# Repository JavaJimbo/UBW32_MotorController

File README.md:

# UBW32_MotorController
Motor control board based on PIC 32MX795 which provides PWM outputs to Cytron MD13s Boards

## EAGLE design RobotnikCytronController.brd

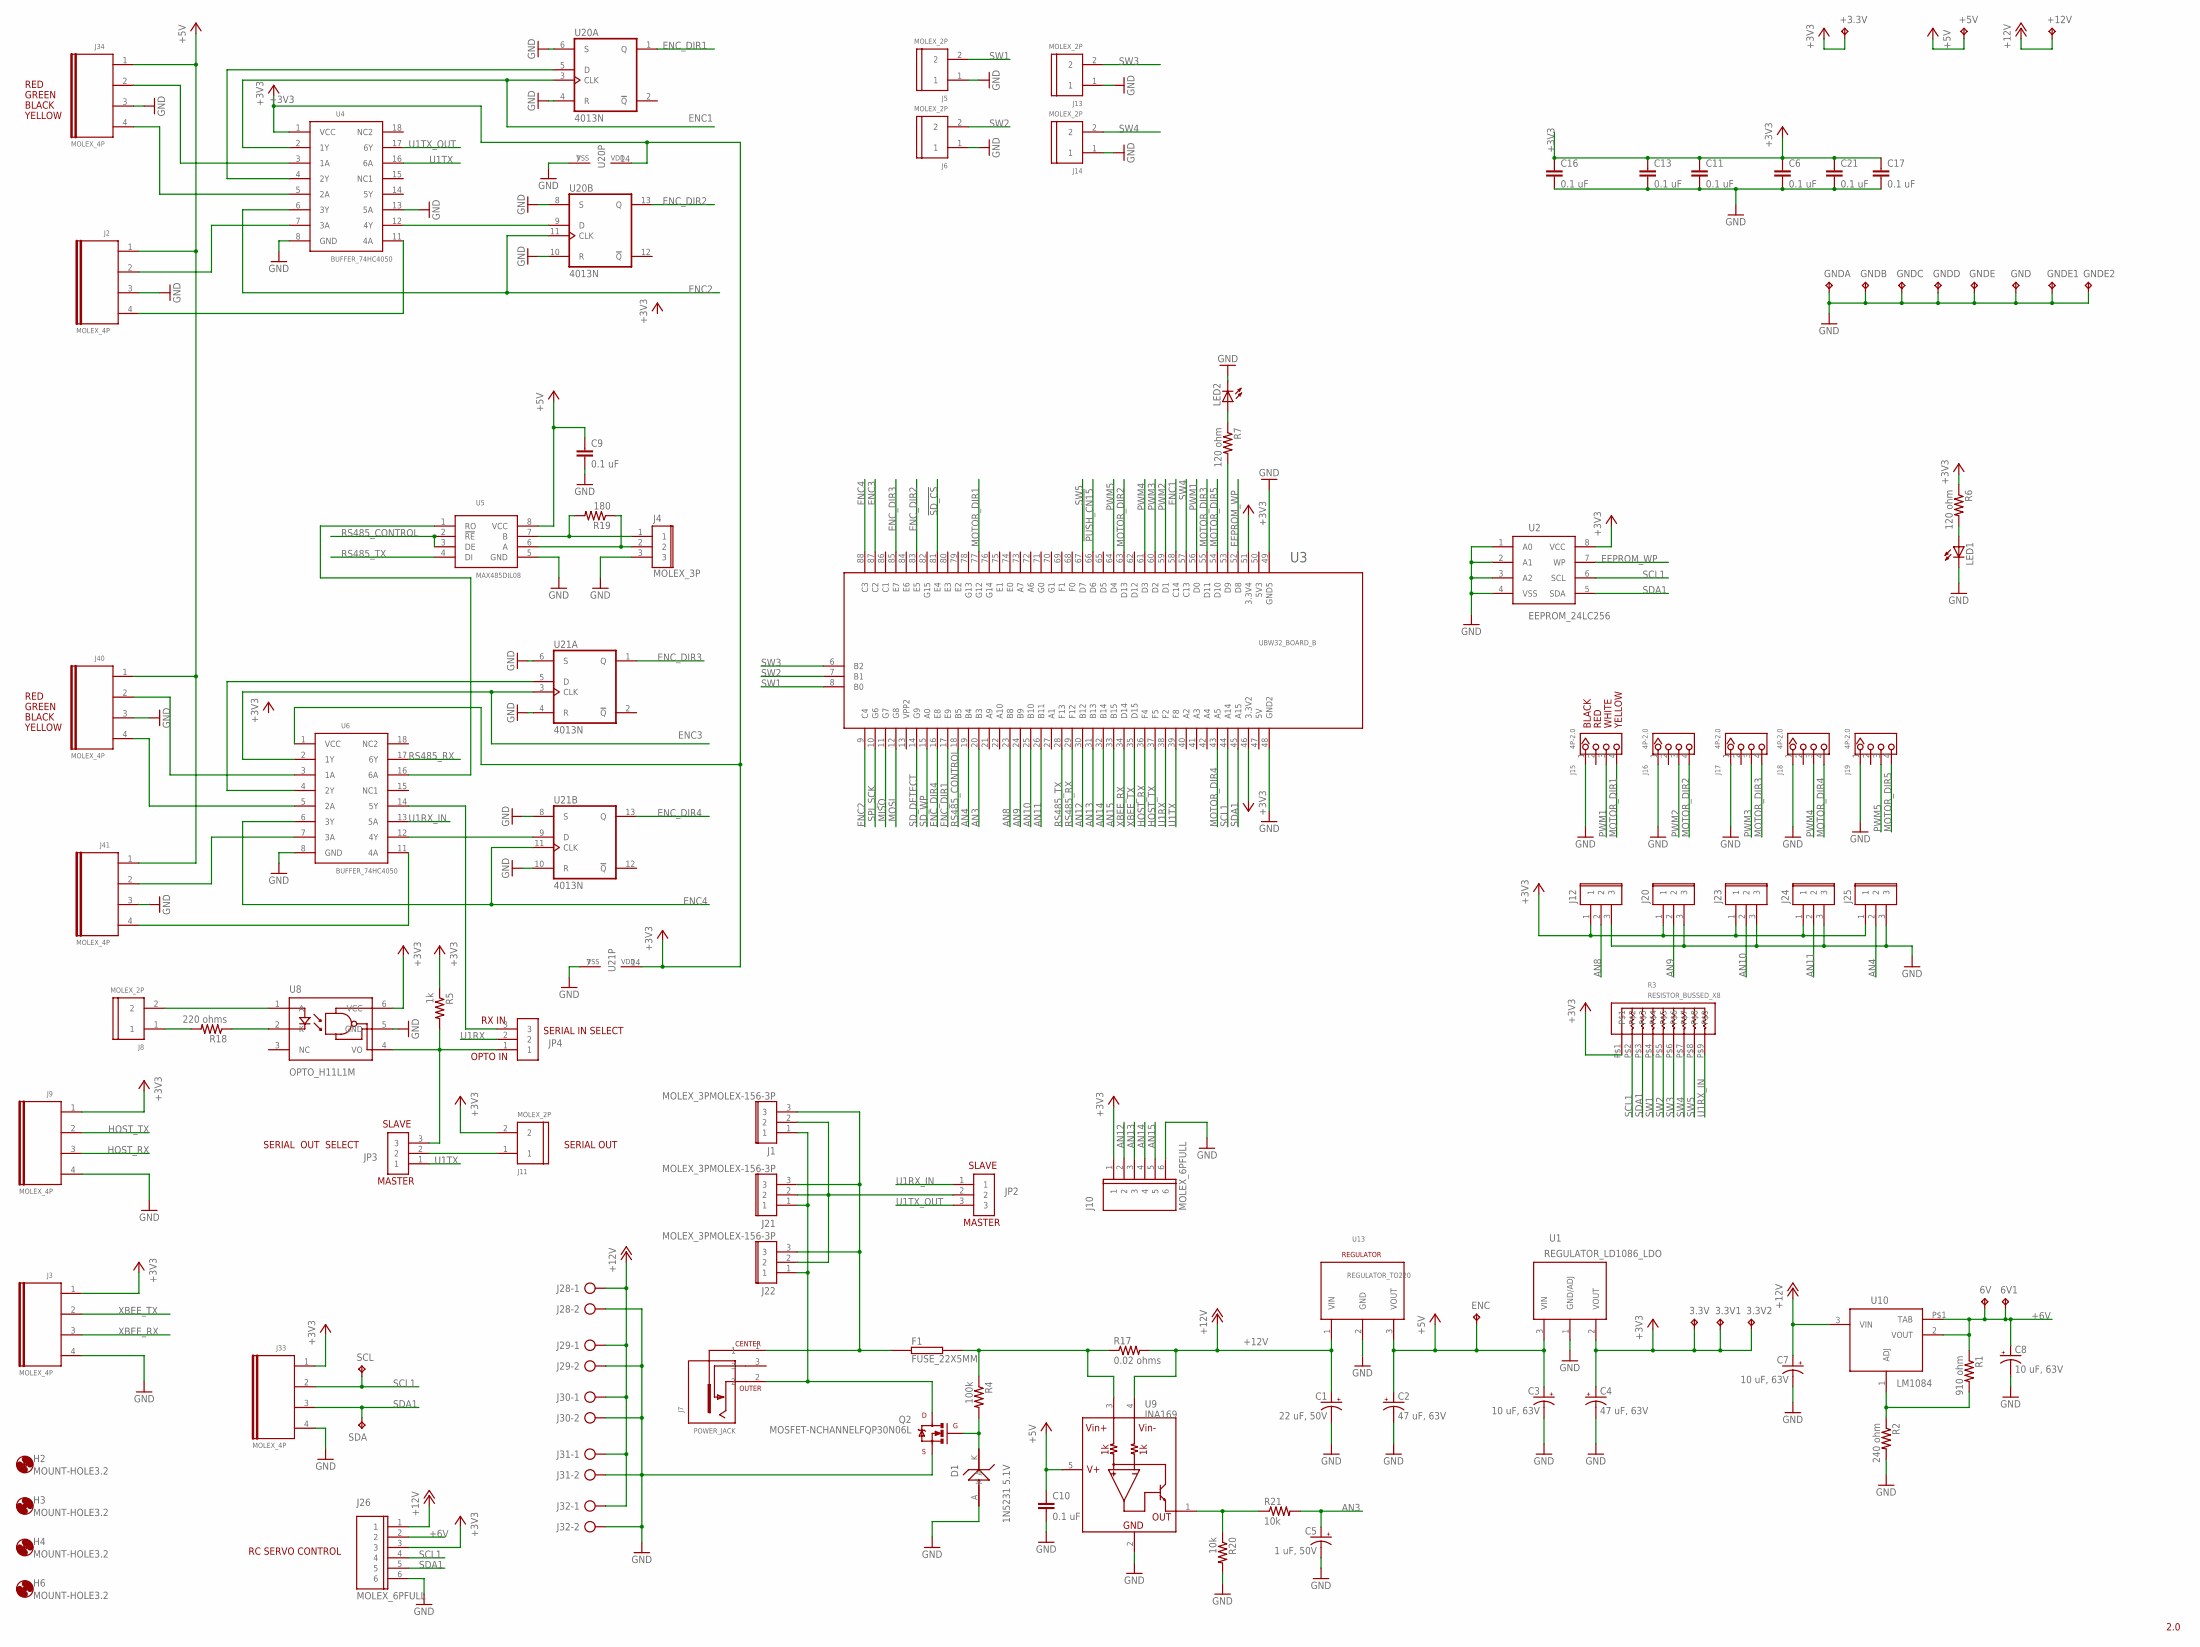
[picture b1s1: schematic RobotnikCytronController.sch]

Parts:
3.3V, 3.3V1, 3.3V2, 6V, 6V1: TPPAD1-13; P1-13
+3.3V, +5V, +12V: TPPAD1-13; P1-13
C1: 22 uF, 50V; POLCAP_2MM
C2, C4: 47 uF, 63V; POLCAP_2MM
C3, C7, C8: 10 uF, 63V; POLCAP_2MM
C5: 1 uF, 50V; POLCAP_2MM
C6, C9, C10, C11, C13, C16, C17, C21: 0.1 uF; C5B2.5
D1: 1N5231 5.1V; T-18_THRU
ENC: TPPAD1-13; P1-13
F1: FUSE_22X5MM; SH22,5
GND: TPPAD1-13; P1-13
GNDA: TPPAD1-13; P1-13
GNDB: TPPAD1-13; P1-13
GNDC: TPPAD1-13; P1-13
GNDD: TPPAD1-13; P1-13
GNDE, GNDE1, GNDE2: TPPAD1-13; P1-13
H2, H3, H4, H6: MOUNT-HOLE3.2; 3,2
J1, J21, J22: MOLEX_3PMOLEX-156-3P; MOLEX-156-3
J2, J3, J9, J33, J34, J40, J41: MOLEX_4P; MOLEX_4P_SLIM
J4, J12, J20, J23, J24, J25: MOLEX_3P
J5, J6, J8, J11, J13, J14: MOLEX_2P
J7: POWER_JACK; POWER_JACK_PJ-202A
J10, J26: MOLEX_6PFULL; MOLEX_6P
J15, J16, J17, J18, J19: 4P-2.0; HW4-2.0
J28, J29, J30, J31, J32: TRMBLOCK_5MM_2P
JP2, JP3, JP4: JUMPER_3P; JUMPER_3P_MINI
LED1, LED2: LED5MM
Q2: MOSFET-NCHANNELFQP30N06L; TO220V
R1: 910 ohm; 1/4_WATT
R2: 240 ohm; 1/4_WATT
R3: RESISTOR_BUSSED_X8; RESISTOR_BUSSED
R4: 100k; 1/4_WATT
R5: 1k; 1/4_WATT
R6, R7: 120 ohm; 1/4_WATT
R17: 0.02 ohms; CURRENT_SENSE
R18: 220 ohms; 1/4_WATT
R19: 180; 1/4_WATT
R20, R21: 10k; 1/4_WATT
SCL: TPPAD1-13; P1-13
SDA: TPPAD1-13; P1-13
U1: REGULATOR_LD1086_LDO; D2PAK
U2: EEPROM_24LC256; DIL08
U3: UBW32_BOARD_B; UBW32_B
U4, U6: BUFFER_74HC4050; DIL18
U5: MAX485DIL08; DIL08
U8: OPTO_H11L1M; DIP_6P
U9: INA169; SOT23-5
U10: LM1084; TO220_HEATSINK
U13: REGULATOR_TO220; TO220V
U20, U21: 4013N; DIL14

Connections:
5V: U3.47 (5V)
5V3: U3.50 (5V3)
!PUSH_CN15: U3.66 (D6)
!SD_CS: U3.81 (E4)
+3V3: 3.3V.TP, 3.3V1.TP, 3.3V2.TP, +3.3V.TP, C4.+, C6.1, C11.1, C13.1, C16.1, C17.1, C21.1, J3.1, J9.1, J10.1, J11.2, J12.1, J20.1, J23.1, J24.1, J25.1, J26.3, J33.1, R3.P$1, R5.1, R6.1, U1.2 (VOUT), U2.8 (VCC), U3.46 (3.3V2), U3.51 (3.3V4), U4.1 (VCC), U6.1 (VCC), U8.6 (VCC), U20.14 (VDD), U21.14 (VDD)
+5V: +5V.TP, C2.+, C3.+, C9.1, C10.1, ENC.TP, J2.1, J34.1, J40.1, J41.1, U1.3 (VIN), U5.8 (VCC), U9.5 (V+), U13.3 (VOUT)
+6V: 6V.TP, 6V1.TP, C8.+, J26.2, R1.1, U10.2 (VOUT), U10.P$1 (TAB)
+12V: +12V.TP, C1.+, C7.+, J26.1, J28.1, J29.1, J30.1, J31.1, J32.1, R17.2, U9.4 (VIN-), U10.3 (VIN), U13.1 (VIN)
AN3: C5.+, R21.2, U3.20 (B3)
AN4: J25.2, U3.19 (B4)
AN8: J12.2, U3.23 (B8)
AN9: J20.2, U3.24 (B9)
AN10: J23.2, U3.25 (B10)
AN11: J24.2, U3.26 (B11)
AN12: J10.2, U3.30 (B12)
AN13: J10.3, U3.31 (B13)
AN14: J10.4, U3.32 (B14)
AN15: J10.5, U3.33 (B15)
EEPROM_WP: U2.7 (WP), U3.52 (D8)
ENC1: U3.58 (C14), U4.2 (1Y), U20.3 (CLK)
ENC2: U3.9 (C4), U4.6 (3Y), U20.11 (CLK)
ENC3: U3.87 (C2), U6.2 (1Y), U21.3 (CLK)
ENC4: U3.88 (C3), U6.6 (3Y), U21.11 (CLK)
ENC_DIR1: U3.17 (E9), U20.1 (Q)
ENC_DIR2: U3.83 (E5), U20.13 (Q)
ENC_DIR3: U3.85 (E7), U21.1 (Q)
ENC_DIR4: U3.16 (E8), U21.13 (Q)
GND: C1.-, C2.-, C3.-, C4.-, C5.-, C6.2, C7.-, C8.-, C9.2, C10.2, C11.2, C13.2, C16.2, C17.2, C21.2, D1.A, GND.TP, GNDA.TP, GNDB.TP, GNDC.TP, GNDD.TP, GNDE.TP, GNDE1.TP, GNDE2.TP, J2.3, J3.4, J4.3, J5.1, J6.1, J9.4, J10.6, J12.3, J13.1, J14.1, J15.1, J16.1, J17.1, J18.1, J19.1, J20.3, J23.3, J24.3, J25.3, J26.6, J28.2, J29.2, J30.2, J31.2, J32.2, J33.4, J34.3, J40.3, J41.3, LED1.K (C), LED2.K (C), Q2.3 (S), R2.2, R20.2, U1.1 (GND/ADJ), U2.1 (A0), U2.2 (A1), U2.3 (A2), U2.4 (VSS), U3.48 (GND2), U3.49 (GND5), U4.8 (GND), U4.13 (5A), U5.5 (GND), U6.8 (GND), U8.5 (GND), U9.2 (GND), U13.2 (GND), U20.4 (R), U20.6 (S), U20.7 (VSS), U20.8 (S), U20.10 (R), U21.4 (R), U21.6 (S), U21.7 (VSS), U21.8 (S), U21.10 (R)
HOST_RX: J9.3, U3.36 (F4)
HOST_TX: J9.2, U3.37 (F5)
MISO: U3.11 (G7)
MOSI: U3.12 (G8)
MOTOR_DIR1: J15.4, U3.77 (G12)
MOTOR_DIR2: J16.4, U3.63 (D13)
MOTOR_DIR3: J17.4, U3.55 (D11)
MOTOR_DIR4: J18.4, U3.43 (A5)
MOTOR_DIR5: J19.4, U3.54 (D10)
unnamed: D1.K, Q2.1 (G), R4.2
unnamed: U4.12 (4Y), U20.9 (D)
unnamed: LED1.A, R6.2
unnamed: J1.1, J7.2, J21.1, J22.1, Q2.2 (D)
unnamed: J11.1, JP3.2
unnamed: JP4.3, U6.14 (5Y)
unnamed: J34.2, U4.3 (1A)
unnamed: U5.1 (RO), U6.16 (6A)
unnamed: F1.1, J1.3, J7.1, J21.3, J22.3
unnamed: U4.4 (2Y), U20.5 (D)
unnamed: J34.4, U4.5 (2A)
unnamed: R7.2, U3.53 (D9)
unnamed: LED2.A, R7.1
unnamed: J2.2, U4.7 (3A)
unnamed: J2.4, U4.11 (4A)
unnamed: R1.2, R2.1, U10.1 (ADJ)
unnamed: J4.1, R19.2, U5.7 (B)
unnamed: J4.2, R19.1, U5.6 (A)
unnamed: J40.2, U6.3 (1A)
unnamed: J8.1, R18.2
unnamed: U6.4 (2Y), U21.5 (D)
unnamed: J40.4, U6.5 (2A)
unnamed: U6.12 (4Y), U21.9 (D)
unnamed: R18.1, U8.2 (K)
unnamed: J41.2, U6.7 (3A)
unnamed: J41.4, U6.11 (4A)
unnamed: J1.2, J21.2, J22.2, JP2.2
unnamed: J8.2, U8.1 (A)
unnamed: F1.2, R4.1, R17.1, U9.3 (VIN+)
unnamed: R20.1, R21.1, U9.1 (OUT)
OPTO_IN: JP3.3, JP4.1, R5.2, U8.4 (VO)
PWM1: J15.3, U3.56 (D0)
PWM2: J16.3, U3.59 (D1)
PWM3: J17.3, U3.60 (D2)
PWM4: J18.3, U3.61 (D3)
PWM5: J19.3, U3.64 (D4)
RS485_CONTROL: U3.18 (B5), U5.2 (!RE), U5.3 (DE)
RS485_RX: U3.29 (F12)
RS485_TX: U3.28 (F13), U5.4 (DI)
SCL1: J26.4, J33.2, R3.P$2, SCL.TP, U2.6 (SCL), U3.44 (A14)
SDA1: J26.5, J33.3, R3.P$3, SDA.TP, U2.5 (SDA), U3.45 (A15)
SD_DETECT: U3.14 (G9)
SD_WP: U3.15 (A0)
SPI_SCK: U3.10 (G6)
SW1: J5.2, R3.P$4, U3.8 (B0)
SW2: J6.2, R3.P$5, U3.7 (B1)
SW3: J13.2, R3.P$6, U3.6 (B2)
SW4: J14.2, R3.P$7, U3.57 (C13)
SW5: R3.P$8, U3.67 (D7)
U1RX: JP4.2, U3.38 (F2)
U1RX_IN: JP2.1, R3.P$9, U6.13 (5A)
U1TX: JP3.1, U3.39 (F8)
U1TX_OUT: JP2.3
XBEE_RX: J3.3, U3.34 (D14)
XBEE_TX: J3.2, U3.35 (D15)

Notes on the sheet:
2.0
RED
GREEN
BLACK
YELLOW
WHITE
SERIAL IN SELECT
SERIAL OUT
OPTO IN
RX IN
SERIAL OUT SELECT
SLAVE
MASTER
RC SERVO CONTROL

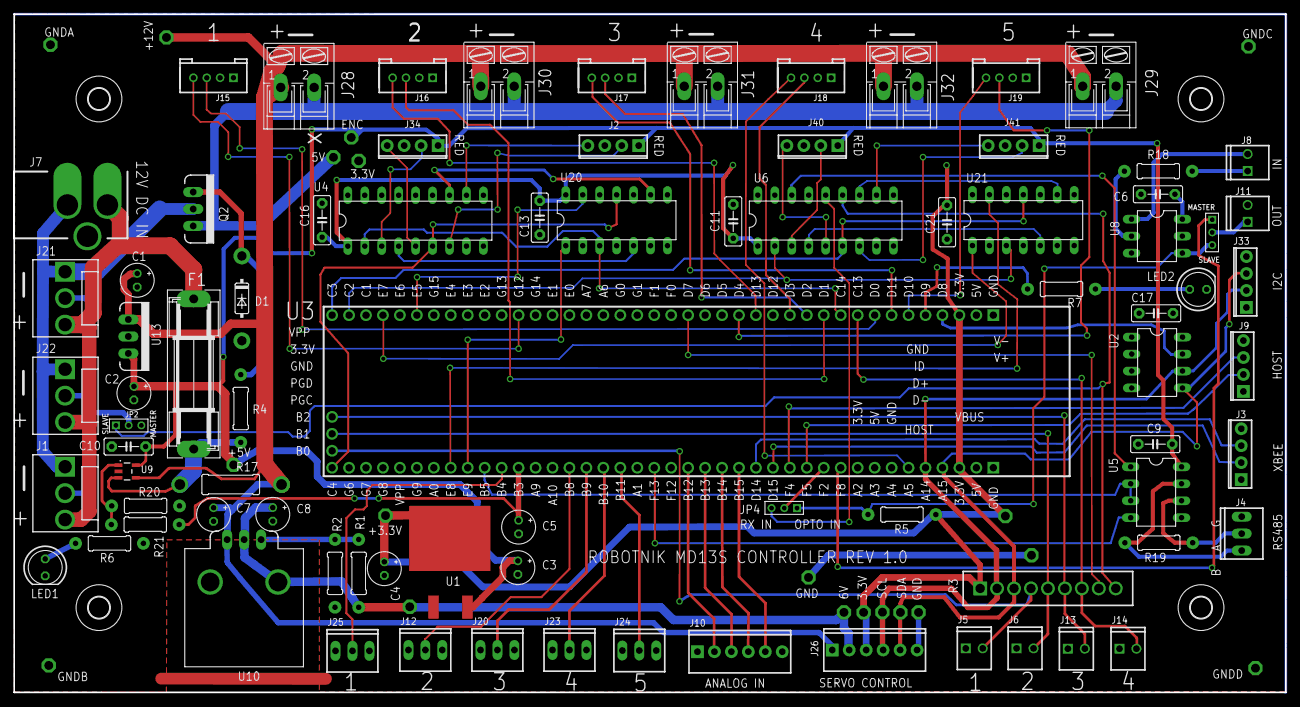
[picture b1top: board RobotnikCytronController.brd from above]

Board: 2 copper layers, 190.5 x 101.6 mm, 105 parts (0 on the bottom side), 81 nets.

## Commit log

2020-07-11 Eagle PCB Files
    This includes the Eagle PCB schematic and PCB files as well as Gerbers for first rev PCB
